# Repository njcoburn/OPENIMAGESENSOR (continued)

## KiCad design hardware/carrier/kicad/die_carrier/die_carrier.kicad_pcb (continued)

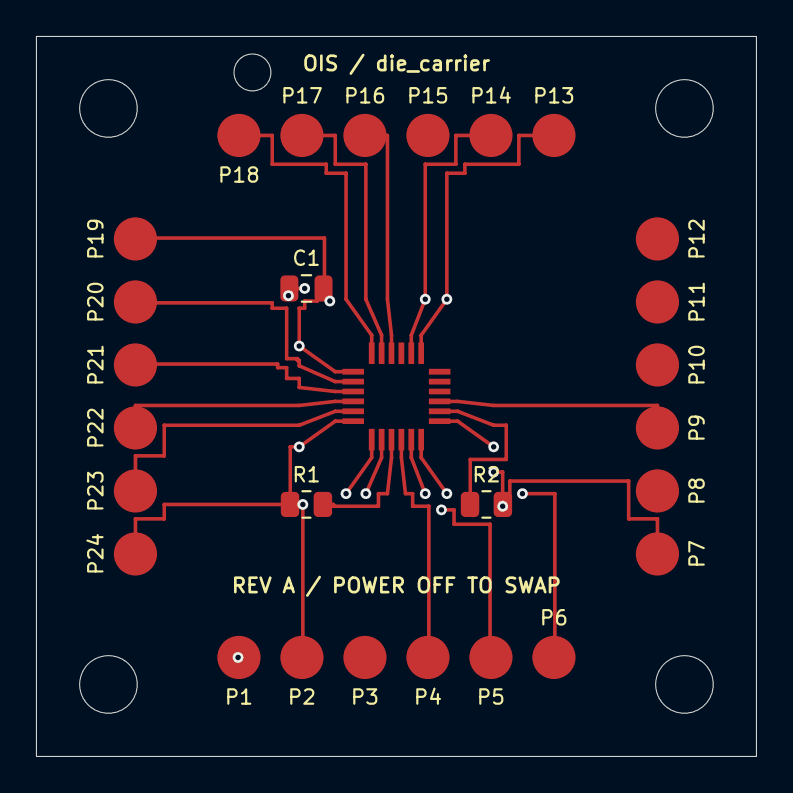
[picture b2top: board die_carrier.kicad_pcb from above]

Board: 4 copper layers, 40.0 x 40.0 mm, 34 parts (0 on the bottom side), 15 nets.

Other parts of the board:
H1: M3 clearance; Mechanical_1
H2: M3 clearance; Mechanical_2
H3: M3 clearance; Mechanical_3
H4: M3 clearance; Mechanical_4
H5: Alignment round; Mechanical_5
H6: Alignment slot; Mechanical_6

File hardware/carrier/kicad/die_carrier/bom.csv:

Reference,Value_or_MPN,Footprint,Note
P1,POGO_TARGET,OIS:Target_2p4,
P2,POGO_TARGET,OIS:Target_2p4,
P3,POGO_TARGET,OIS:Target_2p4,
P4,POGO_TARGET,OIS:Target_2p4,
P5,POGO_TARGET,OIS:Target_2p4,
P6,POGO_TARGET,OIS:Target_2p4,
P7,POGO_TARGET,OIS:Target_2p4,
P8,POGO_TARGET,OIS:Target_2p4,
P9,POGO_TARGET,OIS:Target_2p4,
P10,POGO_TARGET,OIS:Target_2p4,
P11,POGO_TARGET,OIS:Target_2p4,
P12,POGO_TARGET,OIS:Target_2p4,
P13,POGO_TARGET,OIS:Target_2p4,
P14,POGO_TARGET,OIS:Target_2p4,
P15,POGO_TARGET,OIS:Target_2p4,
P16,POGO_TARGET,OIS:Target_2p4,
P17,POGO_TARGET,OIS:Target_2p4,
P18,POGO_TARGET,OIS:Target_2p4,
P19,POGO_TARGET,OIS:Target_2p4,
P20,POGO_TARGET,OIS:Target_2p4,
P21,POGO_TARGET,OIS:Target_2p4,
P22,POGO_TARGET,OIS:Target_2p4,
P23,POGO_TARGET,OIS:Target_2p4,
P24,POGO_TARGET,OIS:Target_2p4,
U1,OIS_3x3_BARE_DIE_PROVISIONAL,OIS:Bond_3x3_PROVISIONAL,Landing pad positions/finish and die attach subject to wire-bond provider; not die pad centers
R1,5.1M 1%,OIS:Resistor_SMD_R_0805_2012Metric,
R2,49.9k 1%,OIS:Resistor_SMD_R_0805_2012Metric,
C1,100n,OIS:Capacitor_SMD_C_0805_2012Metric,

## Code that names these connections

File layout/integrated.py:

"""Integrate saved functional blocks; units micrometres. No optical over-routing."""
from pathlib import Path
import json,hashlib
import klayout.db as k
root=Path(__file__).resolve().parents[1];dest=root/'build/integrated';dest.mkdir(exist_ok=True)
ly=k.Layout();ly.dbu=.001;top=ly.create_cell('sensor_3x3');u=lambda v:round(v/ly.dbu)
sources={}
for filename,name,x,y in [('array-functional.gds','array_3x3',0,100),('readout-functional.gds','column_readout',0,0),('buffer-functional.gds','output_buffer',160,0)]:
 p=root/'checkpoints/integrated'/filename;src=k.Layout();src.read(str(p));cell=ly.create_cell('placed_'+name);cell.copy_tree(src.cell(name));top.insert(k.CellInstArray(cell.cell_index(),k.Trans(u(x),u(y))));sources[filename]=hashlib.sha256(p.read_bytes()).hexdigest()
top.flatten(True)
for li in ly.layer_indexes():
 for s in list(top.shapes(li).each()):
  if s.is_text():s.delete()
top.shapes(ly.layer(0,0)).clear()
M2=(36,0);M3=(42,0);M4=(46,0)
def box(layer,x0,y0,x1,y1):top.shapes(ly.layer(*layer)).insert(k.Box(u(x0),u(y0),u(x1),u(y1)))
def wire(layer,p,q,w=.8):
 assert p[0]==q[0] or p[1]==q[1]
 box(layer,min(p[0],q[0])-w/2,min(p[1],q[1])-w/2,max(p[0],q[0])+w/2,max(p[1],q[1])+w/2)
def via(x,y,upper=False):
 lo,cut,hi=(M3,(40,0),M4) if upper else (M2,(38,0),M3)
 for l in (lo,hi):box(l,x-.4,y-.4,x+.4,y+.4)
 box(cut,x-.13,y-.13,x+.13,y+.13)
ports={}
def label(n,x,y,layer):
 top.shapes(ly.layer(layer[0],10)).insert(k.Text(n,k.Trans(u(x),u(y))));ports[n]=[x,y,layer[0]]
for i in range(3):
 x=75+80*i;y=70+4*i;rx=-16-4*i
 wire(M3,(x,100),(x,y));via(x,y,True)
 wire(M4,(rx,y),(x,y));via(rx,y,True)
 wire(M3,(rx,26+3*i),(rx,y));via(rx,26+3*i)
 wire(M2,(rx,26+3*i),(0,26+3*i));label(f'COL{i}',x,100,M3)
# Mux output to buffer input, routed above both blocks.
wire(M2,(145,35),(150,35));via(150,35);wire(M3,(150,35),(150,64));via(150,64,True)
wire(M4,(150,64),(160,64));via(160,64,True);wire(M3,(160,49),(160,64));via(160,49);label('OUT',150,64,M4)
# Separate shared supply and ground buses, with trunks into all relevant blocks.
for net,y,ax,bx,by in [('GND',84,-10,290,40),('VDD',88,-4,294,43)]:
 wire(M4,(-36,y),(bx,y),2)
 wire(M3,(ax,100),(ax,y),1);via(ax,y,True)
 wire(M2,(280,by),(bx,by),1);via(bx,by);wire(M3,(bx,by),(bx,y),1);via(bx,y,True)
 label(net,-36,y,M4)
wire(M2,(-32,20),(0,20),1);via(-32,20);wire(M3,(-32,20),(-32,84),1);via(-32,84,True)
label('VRESET',-7,100,M3)
for r in range(3):
 for n,dy in [('RST',29),('ROW',32)]:label(f'{n}{r}',0,100+50*r+dy,M2)
for n,y in [('BIAS',23),('SEL0',38),('SEL1',41),('SEL2',44)]:label(n,0,y,M2)
for n,y in [('PREF',46),('BUF',52)]:label(n,280,y,M2)
ly.write(str(dest/'sensor-functional.gds'))
# Keep light windows clear of fill on every filled conductor layer.
optical=k.Region()
for row in range(3):
 for col in range(3):optical.insert(k.Box(u(60+80*col-13),u(105+50*row-13),u(60+80*col+13),u(105+50*row+13)))
def region(layer):return k.Region(top.begin_shapes_rec(ly.layer(*layer)))
assert (region(M4)&optical).is_empty(), 'Inter-block routes must avoid optical keepouts'
comp=region((22,0));bounds=k.Box(u(-38),u(5),u(298),u(248))
for layer,size,pitch in [((30,0),2,4),((34,0),1.2,1.5),((36,0),1.2,1.5),((42,0),1.2,1.5),((46,0),1.2,1.5),((81,0),1.2,1.8)]:
 forbidden=region(layer).sized(u(1 if layer==(30,0) else .4))|optical
 if layer==(30,0):forbidden|=comp.sized(u(1))
 fill=k.Region()
 for x in range(bounds.left+u(1),bounds.right-u(size),u(pitch)):
  for y in range(bounds.bottom+u(1),bounds.top-u(size),u(pitch)):
   tile=k.Box(x,y,x+u(size),y+u(size))
   if (k.Region(tile)&forbidden).is_empty():fill.insert(tile)
 top.shapes(ly.layer(*layer)).insert(fill)
ly.write(str(dest/'sensor_3x3.gds'))
(dest/'placement.json').write_text(json.dumps({'source_sha256':sources,'ports':ports,'array_translation_um':[0,100],'readout_translation_um':[0,0],'buffer_translation_um':[160,0],'fill_bounds_um':[-38,5,298,248]},indent=2)+'\n')

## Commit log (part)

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2025-10-23 gitignore update
2025-10-23 Add first pass at the gdsfactory cell
2025-10-23 update gitignore
2025-10-23 Added N+ Contact to Nwell photodiode area
2025-10-24 getting nfet connected to photodiode
2025-10-25 got auto routing to work on the transistors
2025-10-26 Add row select transistor
2025-11-11 basically finish pixel array
2025-11-21 Make the array
2025-12-14 Full tile grid
